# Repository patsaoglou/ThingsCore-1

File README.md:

#   ThingsCore 1

Linux capable mPCIe SOM based on the STM32MP1 MPU with 512MB DDR3+WIFI+ETHERNET capabilities

## Figures - Coming Soon

- Realistic View

- Stack-up (6-layer PCB)

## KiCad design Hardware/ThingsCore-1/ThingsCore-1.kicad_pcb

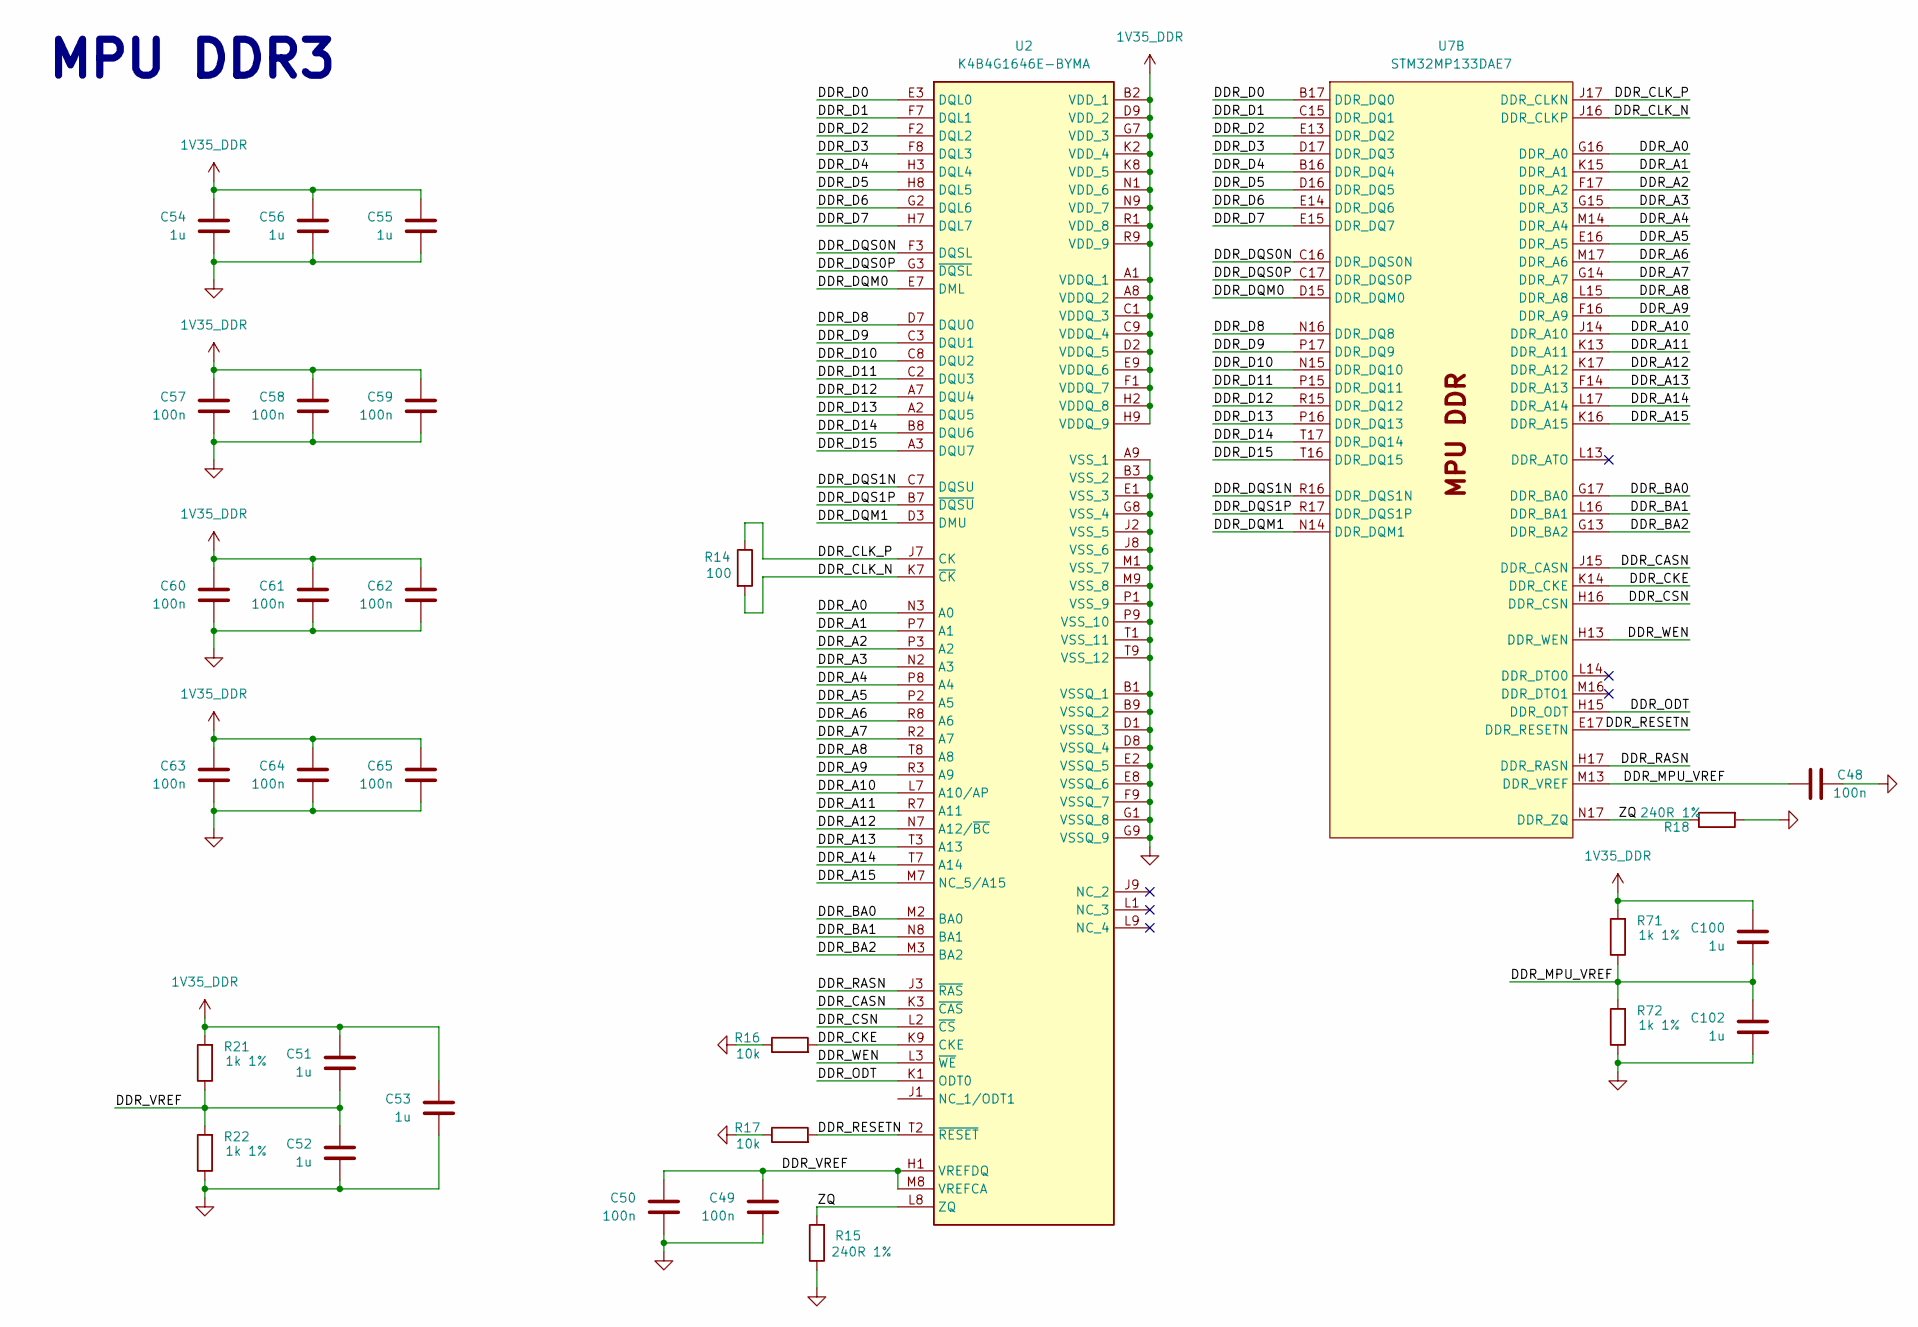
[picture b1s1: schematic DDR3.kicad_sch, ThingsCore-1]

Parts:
C48, C49, C50, C57, C58, C59, C60, C61, C62, C63, C64, C65: 100n; C_0402_1005Metric
C51, C52, C53, C54, C55, C56, C100, C102: 1u; C_0402_1005Metric
R14: 100; R_0402_1005Metric
R15, R18: 240R 1%; R_0402_1005Metric
R16, R17: 10k; R_0402_1005Metric
R21, R22, R71, R72: 1k 1%; R_0402_1005Metric
U2: K4B4G1646E-BYMA; BGA96C80P9X16_750X1330X120; Manufacturer_Part_Number K4B4G1646E-BYMA
U7: STM32MP133DAE7; LFBGA-289_14x14mm_Layout17x17_P0.8mm

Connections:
1V35_DDR: C51.2, C53.2, C54.2, C55.2, C56.2, C57.2, C58.2, C59.2, C60.2, C61.2, C62.2, C63.2, C64.2, C65.2, C100.2, R21.2, R71.2, U2.A1 (VDDQ_1), U2.A8 (VDDQ_2), U2.B2 (VDD_1), U2.C1 (VDDQ_3), U2.C9 (VDDQ_4), U2.D2 (VDDQ_5), U2.D9 (VDD_2), U2.E9 (VDDQ_6), U2.F1 (VDDQ_7), U2.G7 (VDD_3), U2.H2 (VDDQ_8), U2.H9 (VDDQ_9), U2.K2 (VDD_4), U2.K8 (VDD_5), U2.N1 (VDD_6), U2.N9 (VDD_7), U2.R1 (VDD_8), U2.R9 (VDD_9); also elsewhere on the board
/DDR3/DDR_A0: U2.N3 (A0), U7.G16 (DDR_A0)
/DDR3/DDR_A1: U2.P7 (A1), U7.K15 (DDR_A1)
/DDR3/DDR_A2: U2.P3 (A2), U7.F17 (DDR_A2)
/DDR3/DDR_A3: U2.N2 (A3), U7.G15 (DDR_A3)
/DDR3/DDR_A4: U2.P8 (A4), U7.M14 (DDR_A4)
/DDR3/DDR_A5: U2.P2 (A5), U7.E16 (DDR_A5)
/DDR3/DDR_A6: U2.R8 (A6), U7.M17 (DDR_A6)
/DDR3/DDR_A7: U2.R2 (A7), U7.G14 (DDR_A7)
/DDR3/DDR_A8: U2.T8 (A8), U7.L15 (DDR_A8)
/DDR3/DDR_A9: U2.R3 (A9), U7.F16 (DDR_A9)
/DDR3/DDR_A10: U2.L7 (A10/AP), U7.J14 (DDR_A10)
/DDR3/DDR_A11: U2.R7 (A11), U7.K13 (DDR_A11)
/DDR3/DDR_A12: U2.N7 (A12/~BC), U7.K17 (DDR_A12)
/DDR3/DDR_A13: U2.T3 (A13), U7.F14 (DDR_A13)
/DDR3/DDR_A14: U2.T7 (A14), U7.L17 (DDR_A14)
/DDR3/DDR_A15: U2.M7 (NC_5/A15), U7.K16 (DDR_A15)
/DDR3/DDR_BA0: U2.M2 (BA0), U7.G17 (DDR_BA0)
/DDR3/DDR_BA1: U2.N8 (BA1), U7.L16 (DDR_BA1)
/DDR3/DDR_BA2: U2.M3 (BA2), U7.G13 (DDR_BA2)
/DDR3/DDR_CASN: U2.K3 (~CAS), U7.J15 (DDR_CASN)
/DDR3/DDR_CKE: R16.2, U2.K9 (CKE), U7.K14 (DDR_CKE)
/DDR3/DDR_CLK_N: R14.2, U2.K7 (~CK), U7.J16 (DDR_CLKP)
/DDR3/DDR_CLK_P: R14.1, U2.J7 (CK), U7.J17 (DDR_CLKN)
/DDR3/DDR_CSN: U2.L2 (~CS), U7.H16 (DDR_CSN)
/DDR3/DDR_D0: U2.E3 (DQL0), U7.B17 (DDR_DQ0)
/DDR3/DDR_D1: U2.F7 (DQL1), U7.C15 (DDR_DQ1)
/DDR3/DDR_D2: U2.F2 (DQL2), U7.E13 (DDR_DQ2)
/DDR3/DDR_D3: U2.F8 (DQL3), U7.D17 (DDR_DQ3)
/DDR3/DDR_D4: U2.H3 (DQL4), U7.B16 (DDR_DQ4)
/DDR3/DDR_D5: U2.H8 (DQL5), U7.D16 (DDR_DQ5)
/DDR3/DDR_D6: U2.G2 (DQL6), U7.E14 (DDR_DQ6)
/DDR3/DDR_D7: U2.H7 (DQL7), U7.E15 (DDR_DQ7)
/DDR3/DDR_D8: U2.D7 (DQU0), U7.N16 (DDR_DQ8)
/DDR3/DDR_D9: U2.C3 (DQU1), U7.P17 (DDR_DQ9)
/DDR3/DDR_D10: U2.C8 (DQU2), U7.N15 (DDR_DQ10)
/DDR3/DDR_D11: U2.C2 (DQU3), U7.P15 (DDR_DQ11)
/DDR3/DDR_D12: U2.A7 (DQU4), U7.R15 (DDR_DQ12)
/DDR3/DDR_D13: U2.A2 (DQU5), U7.P16 (DDR_DQ13)
/DDR3/DDR_D14: U2.B8 (DQU6), U7.T17 (DDR_DQ14)
/DDR3/DDR_D15: U2.A3 (DQU7), U7.T16 (DDR_DQ15)
/DDR3/DDR_DQM0: U2.E7 (DML), U7.D15 (DDR_DQM0)
/DDR3/DDR_DQM1: U2.D3 (DMU), U7.N14 (DDR_DQM1)
/DDR3/DDR_DQS0N: U2.F3 (DQSL), U7.C16 (DDR_DQS0N)
/DDR3/DDR_DQS0P: U2.G3 (~DQSL), U7.C17 (DDR_DQS0P)
/DDR3/DDR_DQS1N: U2.C7 (DQSU), U7.R16 (DDR_DQS1N)
/DDR3/DDR_DQS1P: U2.B7 (~DQSU), U7.R17 (DDR_DQS1P)
/DDR3/DDR_MPU_VREF: C48.2, C100.1, C102.2, R71.1, R72.2, U7.M13 (DDR_VREF)
/DDR3/DDR_ODT: U2.K1 (ODT0), U7.H15 (DDR_ODT)
/DDR3/DDR_RASN: U2.J3 (~RAS), U7.H17 (DDR_RASN)
/DDR3/DDR_RESETN: R17.2, U2.T2 (~RESET), U7.E17 (DDR_RESETN)
/DDR3/DDR_VREF: C49.2, C50.2, C51.1, C52.2, R21.1, R22.2, U2.H1 (VREFDQ), U2.M8 (VREFCA)
/DDR3/DDR_WEN: U2.L3 (~WE), U7.H13 (DDR_WEN)
/DDR3/ZQ: R15.2, R18.1, U2.L8 (ZQ), U7.N17 (DDR_ZQ)
GND: C48.1, C49.1, C50.1, C52.1, C53.1, C54.1, C55.1, C56.1, C57.1, C58.1, C59.1, C60.1, C61.1, C62.1, C63.1, C64.1, C65.1, C102.1, R15.1, R16.1, R17.1, R18.2, R22.1, R72.1, U2.A9 (VSS_1), U2.B1 (VSSQ_1), U2.B3 (VSS_2), U2.B9 (VSSQ_2), U2.D1 (VSSQ_3), U2.D8 (VSSQ_4), U2.E1 (VSS_3), U2.E2 (VSSQ_5), U2.E8 (VSSQ_6), U2.F9 (VSSQ_7), U2.G1 (VSSQ_8), U2.G8 (VSS_4), U2.G9 (VSSQ_9), U2.J2 (VSS_5), U2.J8 (VSS_6), U2.M1 (VSS_7), U2.M9 (VSS_8), U2.P1 (VSS_9), U2.P9 (VSS_10), U2.T1 (VSS_11), U2.T9 (VSS_12); also elsewhere on the board

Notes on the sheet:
MPU DDR3

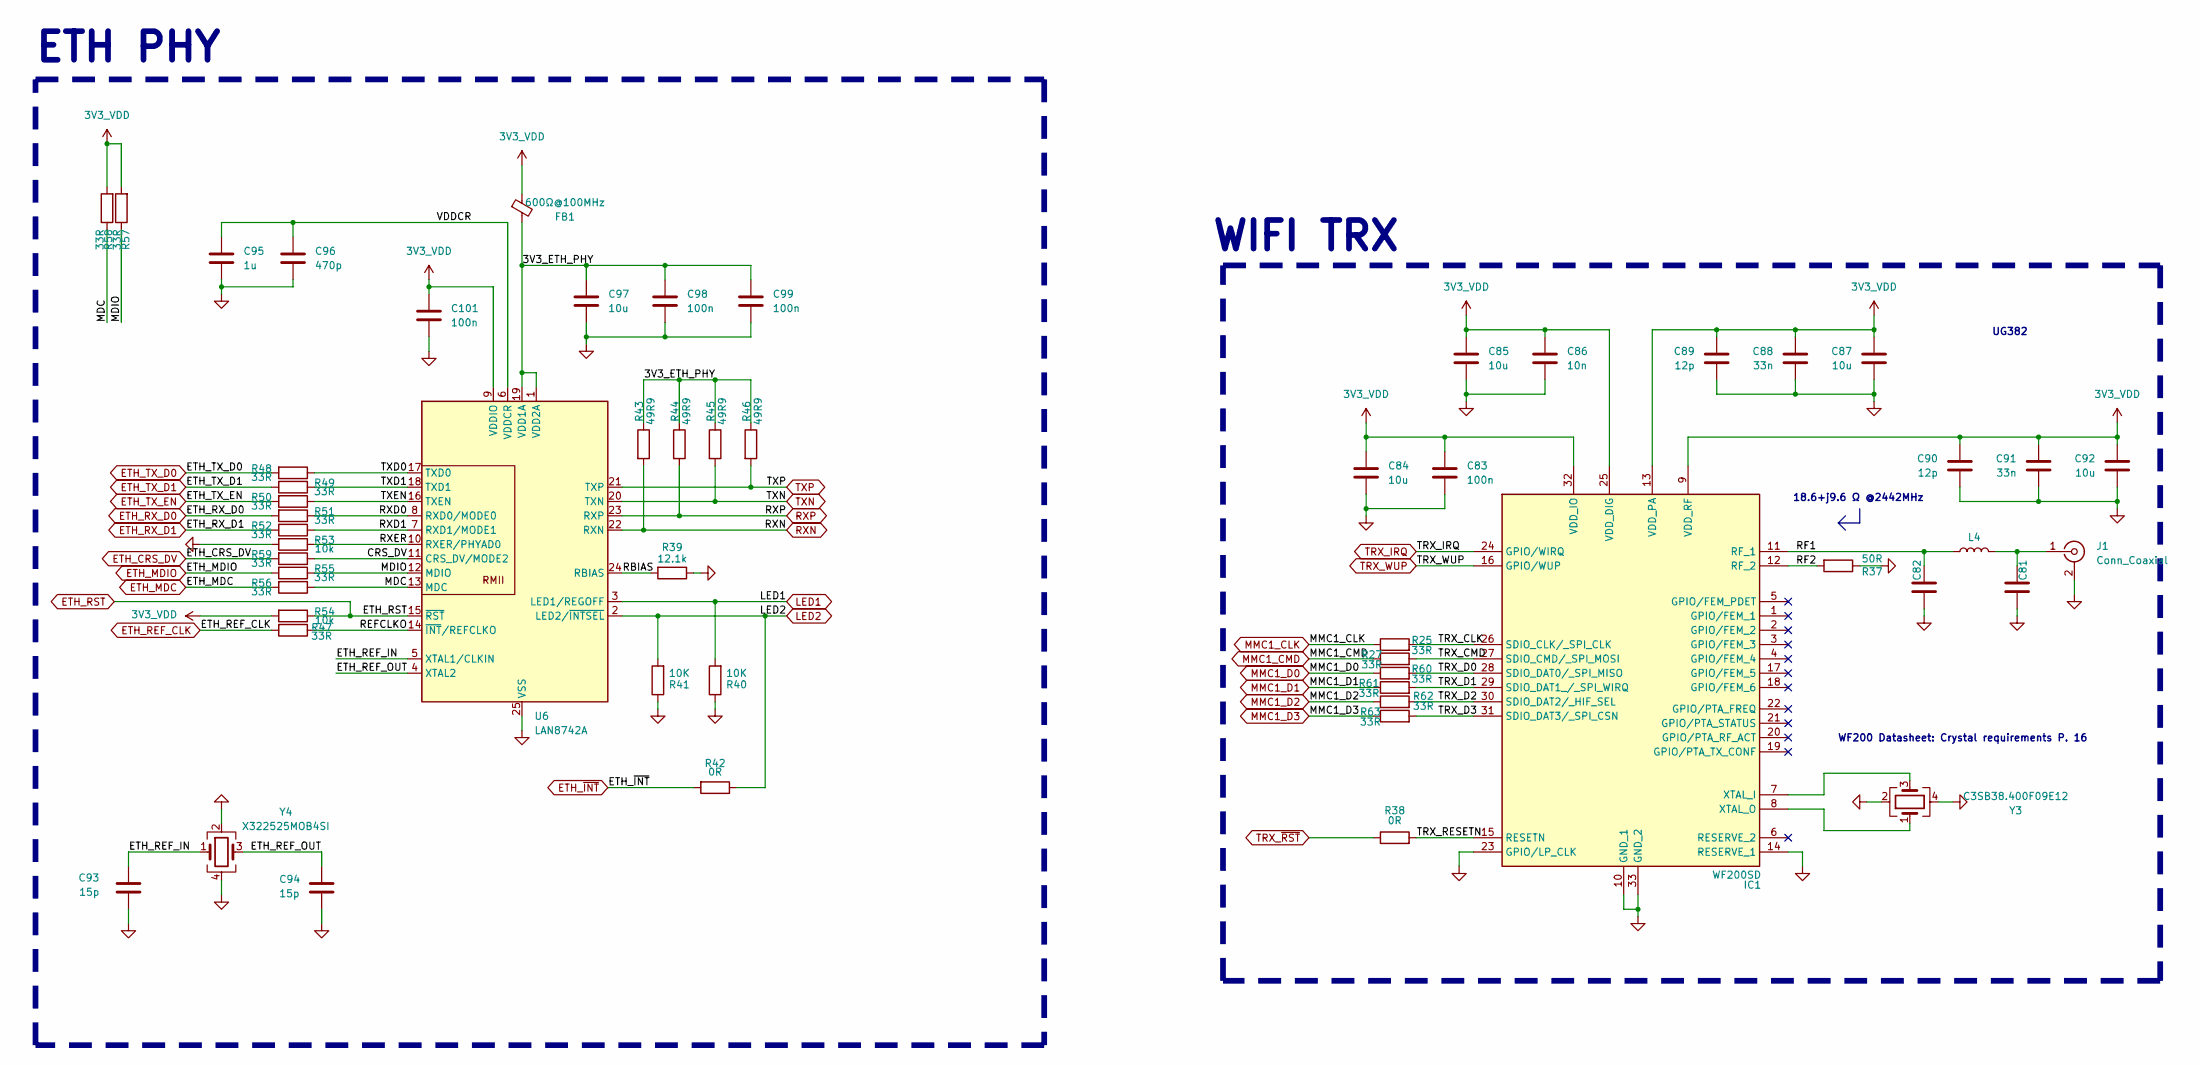
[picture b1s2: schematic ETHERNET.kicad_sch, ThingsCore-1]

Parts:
C81: C_0402_1005Metric
C82: 2.2u; C_0402_1005Metric
C83, C98, C99, C101: 100n; C_0402_1005Metric
C84, C85, C87, C92, C97: 10u; C_0402_1005Metric
C86: 10n; C_0402_1005Metric
C88, C91: 33n; C_0402_1005Metric
C89, C90: 12p; C_0402_1005Metric
C93, C94: 15p; C_0402_1005Metric
C95: 1u; C_0402_1005Metric
C96: 470p; C_0402_1005Metric
FB1: 600Ω@100MHz; L_0805_2012Metric
IC1: WF200SD; QFN40P400X400X90-33N-D; Mouser Part Number 634-WF200SD
J1: Conn_Coaxial; U.FL_Molex_MCRF_73412-0110_Vertical
L4: L_0402_1005Metric
R25, R27, R47, R48, R49, R50, R51, R52, R55, R56, R57, R58, R59, R60, R61, R62, R63: 33R; R_0402_1005Metric
R37: 50R; R_0402_1005Metric
R38, R42: 0R; R_0402_1005Metric
R39: 12.1k; R_0402_1005Metric
R40, R41: 10K; R_0402_1005Metric
R43, R44, R45, R46: 49R9; R_0402_1005Metric
R53, R54: 10k; R_0402_1005Metric
U6: LAN8742A; VQFN-24-1EP_4x4mm_P0.5mm_EP2.45x2.45mm
Y3: C3SB38.400F09E12; Crystal_SMD_3225-4Pin_3.2x2.5mm
Y4: X322525MOB4SI; Crystal_SMD_3225-4Pin_3.2x2.5mm

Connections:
3V3_VDD: C83.2, C84.2, C85.2, C86.2, C87.2, C88.2, C89.2, C90.2, C91.2, C92.2, C101.2, FB1.1, IC1.9 (VDD_RF), IC1.13 (VDD_PA), IC1.25 (VDD_DIG), IC1.32 (VDD_IO), R54.2, R57.2, R58.2, U6.9 (VDDIO); also elsewhere on the board
/NETWORKING/3V3_ETH_PHY: C97.2, C98.2, C99.2, FB1.2, R43.1, R44.1, R45.1, R46.1, U6.1 (VDD2A), U6.19 (VDD1A)
/NETWORKING/CRS_DV: R59.1, U6.11 (CRS_DV/MODE2)
/NETWORKING/ETH_REF_IN: C93.2, U6.5 (XTAL1/CLKIN), Y4.1
/NETWORKING/ETH_REF_OUT: C94.2, U6.4 (XTAL2), Y4.3
/NETWORKING/MDC: R56.1, R58.1, U6.13 (MDC)
/NETWORKING/MDIO: R55.1, R57.1, U6.12 (MDIO)
/NETWORKING/RBIAS: R39.2, U6.24 (RBIAS)
/NETWORKING/REFCLKO: R47.1, U6.14 (~INT/REFCLKO)
/NETWORKING/RF1: C82.1, IC1.11 (RF_1), L4.1
/NETWORKING/RF2: IC1.12 (RF_2), R37.2
/NETWORKING/RXD0: R51.1, U6.8 (RXD0/MODE0)
/NETWORKING/RXD1: R52.1, U6.7 (RXD1/MODE1)
/NETWORKING/RXER: R53.1, U6.10 (RXER/PHYAD0)
/NETWORKING/TRX_CLK: IC1.26 (SDIO_CLK/_SPI_CLK), R25.2
/NETWORKING/TRX_CMD: IC1.27 (SDIO_CMD/_SPI_MOSI), R27.2
/NETWORKING/TRX_D0: IC1.28 (SDIO_DAT0/_SPI_MISO), R60.2
/NETWORKING/TRX_D1: IC1.29 (SDIO_DAT1_/_SPI_WIRQ), R61.2
/NETWORKING/TRX_D2: IC1.30 (SDIO_DAT2/_HIF_SEL), R62.2
/NETWORKING/TRX_D3: IC1.31 (SDIO_DAT3/_SPI_CSN), R63.2
/NETWORKING/TRX_RESETN: IC1.15 (RESETN), R38.2
/NETWORKING/TXD0: R48.1, U6.17 (TXD0)
/NETWORKING/TXD1: R49.1, U6.18 (TXD1)
/NETWORKING/TXEN: R50.1, U6.16 (TXEN)
/NETWORKING/VDDCR: C95.2, C96.2, U6.6 (VDDCR)
ETH_CRS_DV: R59.2; also elsewhere on the board
ETH_MDC: R56.2; also elsewhere on the board
ETH_MDIO: R55.2; also elsewhere on the board
ETH_REF_CLK: R47.2; also elsewhere on the board
ETH_RST: R54.1, U6.15 (~RST); also elsewhere on the board
ETH_RX_D0: R51.2; also elsewhere on the board
ETH_RX_D1: R52.2; also elsewhere on the board
ETH_TX_D0: R48.2; also elsewhere on the board
ETH_TX_D1: R49.2; also elsewhere on the board
ETH_TX_EN: R50.2; also elsewhere on the board
ETH_~INT: R42.2; also elsewhere on the board
GND: C81.2, C82.2, C83.1, C84.1, C85.1, C86.1, C87.1, C88.1, C89.1, C90.1, C91.1, C92.1, C93.1, C94.1, C95.1, C96.1, C97.1, C98.1, C99.1, C101.1, IC1.10 (GND_1), IC1.14 (RESERVE_1), IC1.23 (GPIO/LP_CLK), IC1.33 (GND_2), J1.2 (Ext), R37.1, R39.1, R40.1, R41.1, R53.2, U6.25 (VSS), Y3.2, Y3.4, Y4.2, Y4.4; also elsewhere on the board
LED1: R40.2, U6.3 (LED1/REGOFF); also elsewhere on the board
LED2: R41.2, R42.1, U6.2 (LED2/~INTSEL); also elsewhere on the board
MMC1_CLK: R25.1; also elsewhere on the board
MMC1_CMD: R27.1; also elsewhere on the board
MMC1_D0: R60.1; also elsewhere on the board
MMC1_D1: R61.1; also elsewhere on the board
MMC1_D2: R62.1; also elsewhere on the board
MMC1_D3: R63.1; also elsewhere on the board
unnamed: IC1.7 (XTAL_I), Y3.3
unnamed: IC1.8 (XTAL_O), Y3.1
unnamed: C81.1, J1.1 (In), L4.2
RXN: R43.2, U6.22 (RXN); also elsewhere on the board
RXP: R44.2, U6.23 (RXP); also elsewhere on the board
TRX_IRQ: IC1.24 (GPIO/WIRQ); also elsewhere on the board
TRX_WUP: IC1.16 (GPIO/WUP); also elsewhere on the board
TRX_~RST: R38.1
TXN: R45.2, U6.20 (TXN); also elsewhere on the board
TXP: R46.2, U6.21 (TXP); also elsewhere on the board

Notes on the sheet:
UG382
18.6+j9.6 Ω @2442MHz
WF200 Datasheet: Crystal requirements P. 16
ETH PHY
WIFI TRX

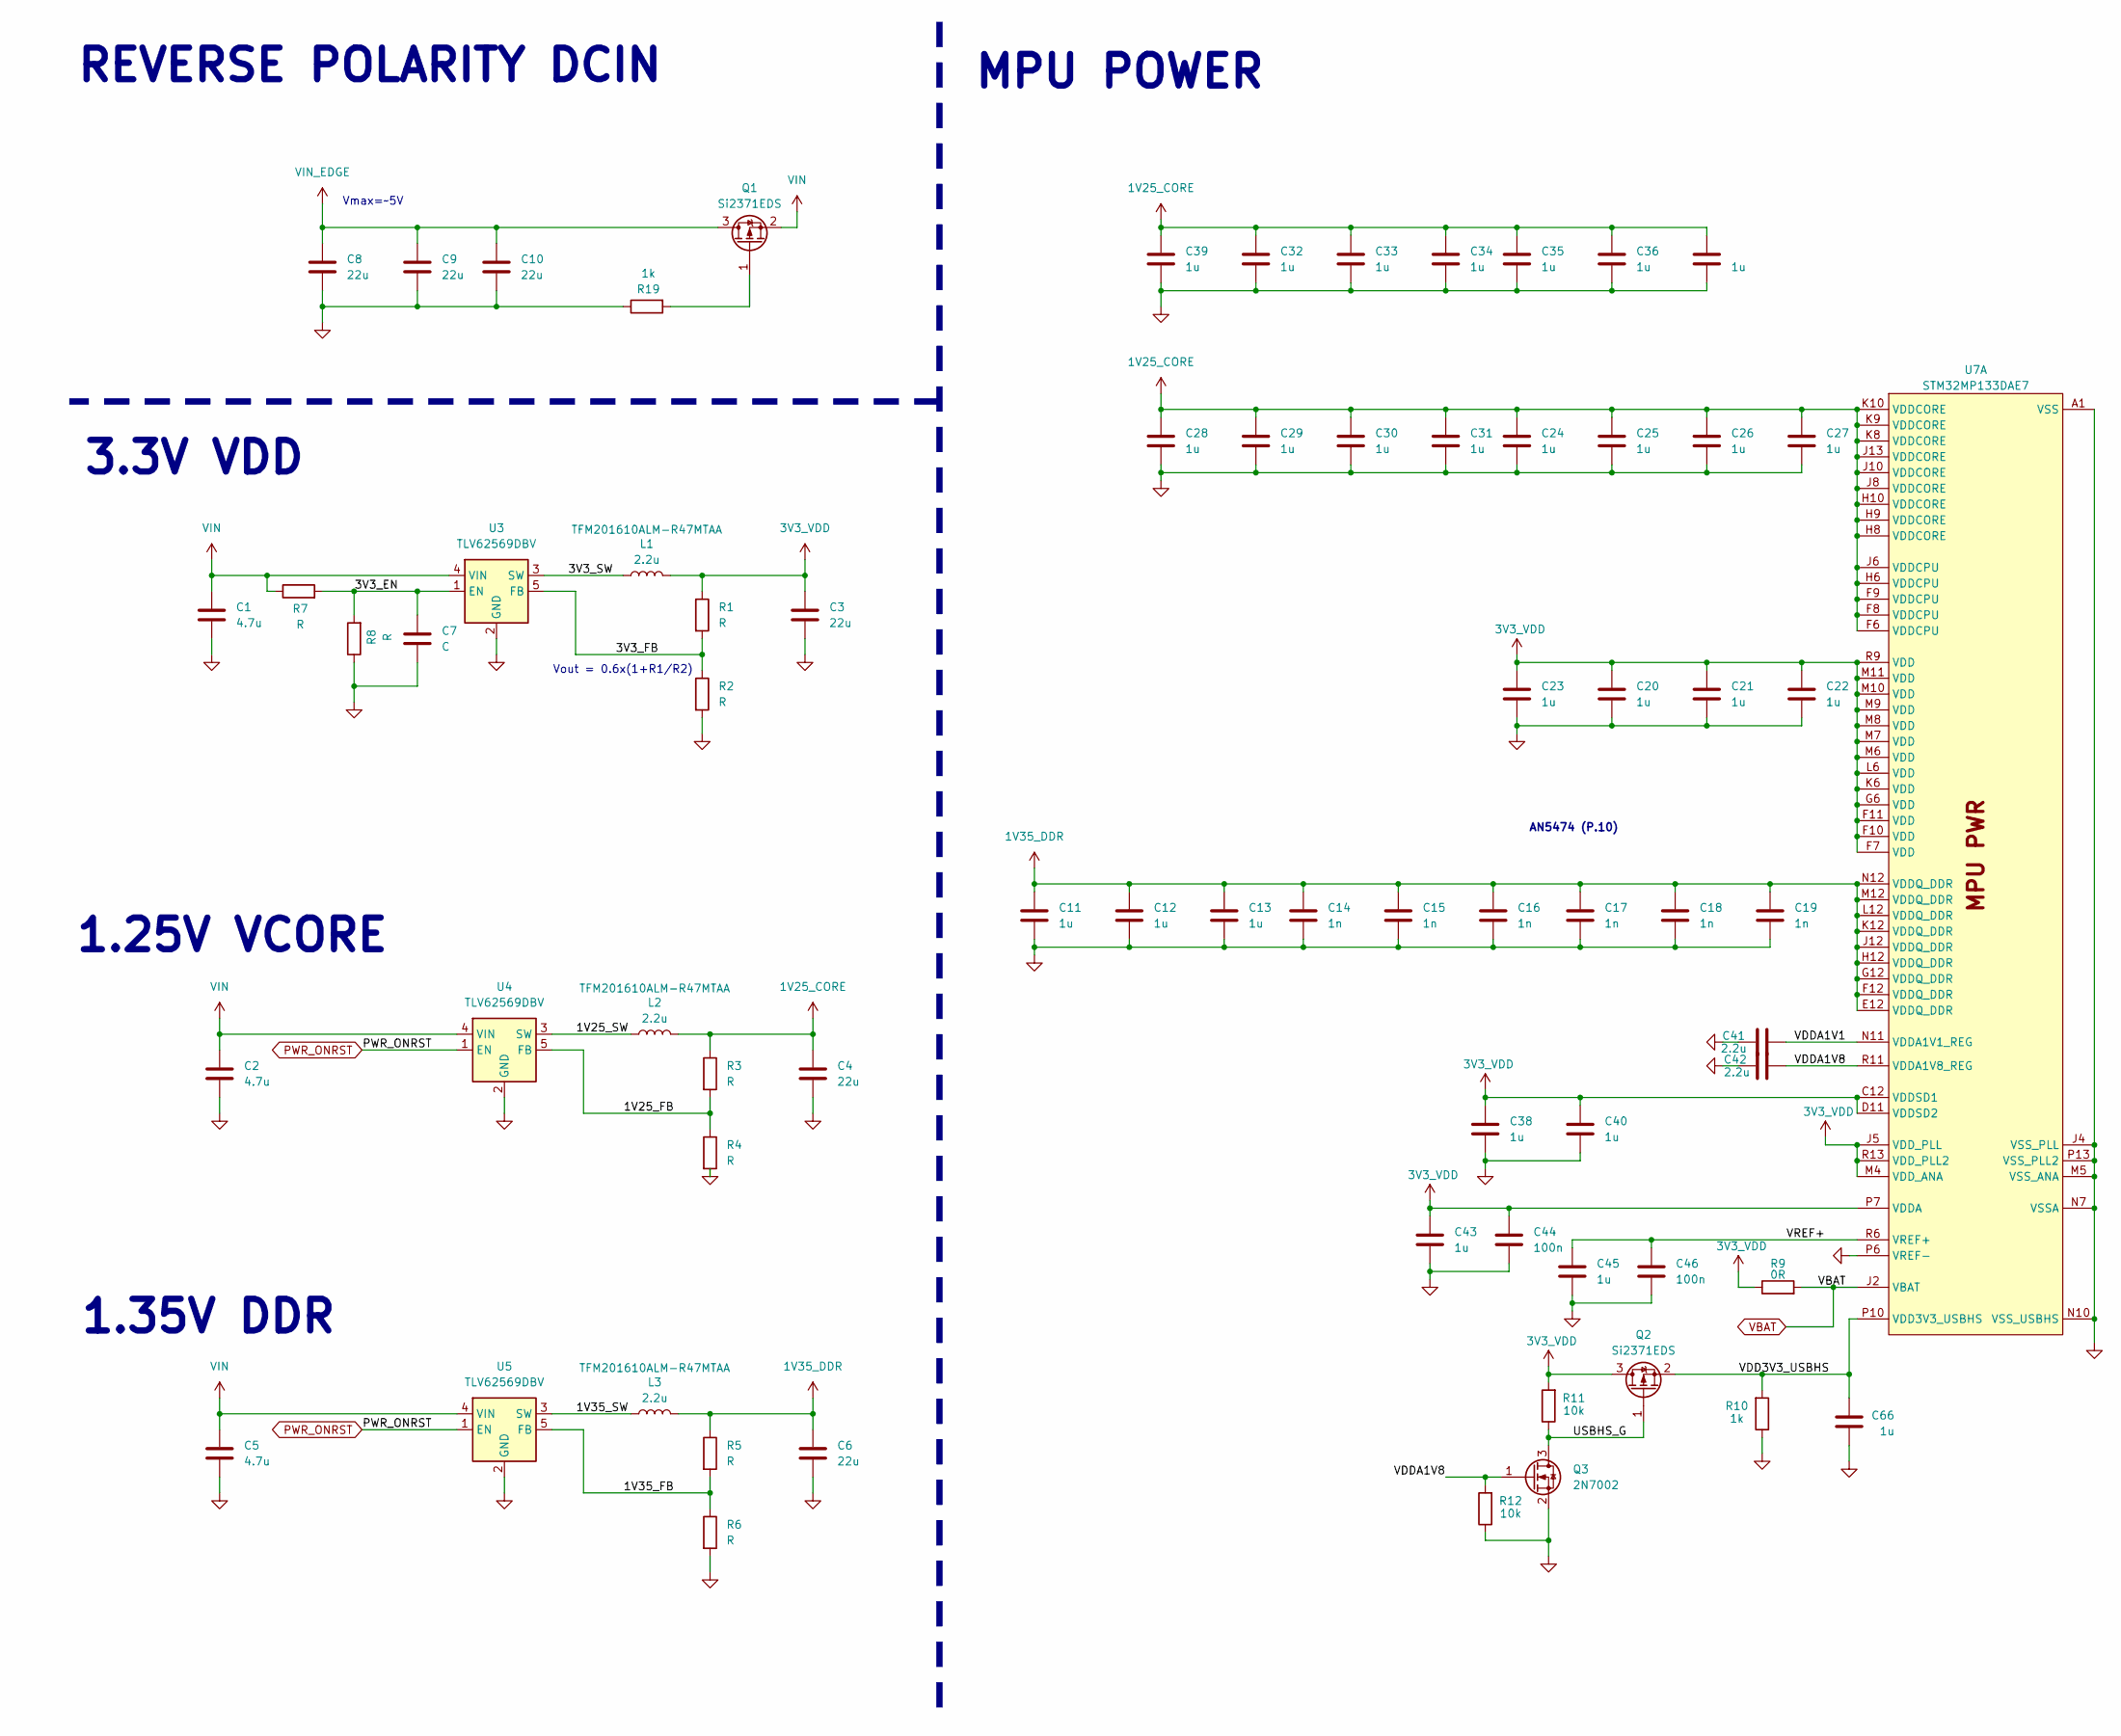
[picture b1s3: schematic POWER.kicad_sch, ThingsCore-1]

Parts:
C1, C2, C5: 4.7u; C_0603_1608Metric
C3, C4, C6, C8, C9, C10: 22u; C_0805_2012Metric
C7: C; C_0402_1005Metric
C11, C12, C13, C20, C21, C22, C23, C24, C25, C26, C27, C28, C29, C30, C31, C32, C33, C34, C35, C36, C37, C38, C39, C40, C43, C45, C66: 1u; C_0402_1005Metric
C14, C15, C16, C17, C18, C19: 1n; C_0402_1005Metric
C41, C42: 2.2u; C_0402_1005Metric
C44, C46: 100n; C_0402_1005Metric
L1, L2, L3: 2.2u; L_0805_2016
Q1, Q2: Si2371EDS; SOT-23
Q3: 2N7002; SOT-23
R1, R2, R3, R4, R5, R6, R7, R8: R; R_0402_1005Metric
R9: 0R; R_0402_1005Metric
R10, R19: 1k; R_0402_1005Metric
R11, R12: 10k; R_0402_1005Metric
U3, U4, U5: TLV62569DBV; SOT-23-5_HandSoldering
U7: STM32MP133DAE7; LFBGA-289_14x14mm_Layout17x17_P0.8mm

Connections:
1V25_CORE: C4.2, C24.2, C25.2, C26.2, C27.2, C28.2, C29.2, C30.2, C31.2, C32.2, C33.2, C34.2, C35.2, C36.2, C37.2, C39.2, L2.2, R3.1, U7.F6 (VDDCPU), U7.F8 (VDDCPU), U7.F9 (VDDCPU), U7.H6 (VDDCPU), U7.H8 (VDDCORE), U7.H9 (VDDCORE), U7.H10 (VDDCORE), U7.J6 (VDDCPU), U7.J8 (VDDCORE), U7.J10 (VDDCORE), U7.J13 (VDDCORE), U7.K8 (VDDCORE), U7.K9 (VDDCORE), U7.K10 (VDDCORE)
1V35_DDR: C6.2, C11.2, C12.2, C13.2, C14.2, C15.2, C16.2, C17.2, C18.2, C19.2, L3.2, R5.1, U7.E12 (VDDQ_DDR), U7.F12 (VDDQ_DDR), U7.G12 (VDDQ_DDR), U7.H12 (VDDQ_DDR), U7.J12 (VDDQ_DDR), U7.K12 (VDDQ_DDR), U7.L12 (VDDQ_DDR), U7.M12 (VDDQ_DDR), U7.N12 (VDDQ_DDR); also elsewhere on the board
3V3_VDD: C3.2, C20.2, C21.2, C22.2, C23.2, C38.2, C40.2, C43.2, C44.2, L1.2, Q2.3 (D), R1.1, R9.1, R11.2, U7.C12 (VDDSD1), U7.D11 (VDDSD2), U7.F7 (VDD), U7.F10 (VDD), U7.F11 (VDD), U7.G6 (VDD), U7.J5 (VDD_PLL), U7.K6 (VDD), U7.L6 (VDD), U7.M4 (VDD_ANA), U7.M6 (VDD), U7.M7 (VDD), U7.M8 (VDD), U7.M9 (VDD), U7.M10 (VDD), U7.M11 (VDD), U7.P7 (VDDA), U7.R9 (VDD), U7.R13 (VDD_PLL2); also elsewhere on the board
/POWER/1V25_FB: R3.2, R4.1, U4.5 (FB)
/POWER/1V25_SW: L2.1, U4.3 (SW)
/POWER/1V35_FB: R5.2, R6.1, U5.5 (FB)
/POWER/1V35_SW: L3.1, U5.3 (SW)
/POWER/3V3_EN: C7.2, R7.2, R8.2, U3.1 (EN)
/POWER/3V3_FB: R1.2, R2.1, U3.5 (FB)
/POWER/3V3_SW: L1.1, U3.3 (SW)
/POWER/USBHS_G: Q2.1 (G), Q3.3 (D), R11.1
/POWER/VDD3V3_USBHS: C66.2, Q2.2 (S), R10.2, U7.P10 (VDD3V3_USBHS)
/POWER/VDDA1V1: C41.1, U7.N11 (VDDA1V1_REG)
/POWER/VDDA1V8: C42.1, Q3.1 (G), R12.2, U7.R11 (VDDA1V8_REG)
/POWER/VREF+: C45.2, C46.2, U7.R6 (VREF+)
GND: C1.1, C2.1, C3.1, C4.1, C5.1, C6.1, C7.1, C8.1, C9.1, C10.1, C11.1, C12.1, C13.1, C14.1, C15.1, C16.1, C17.1, C18.1, C19.1, C20.1, C21.1, C22.1, C23.1, C24.1, C25.1, C26.1, C27.1, C28.1, C29.1, C30.1, C31.1, C32.1, C33.1, C34.1, C35.1, C36.1, C37.1, C38.1, C39.1, C40.1, C41.2, C42.2, C43.1, C44.1, C45.1, C46.1, C66.1, Q3.2 (S), R2.2, R4.2, R6.2, R8.1, R10.1, R12.1, R19.1, U3.2 (GND), U4.2 (GND), U5.2 (GND), U7.A1 (VSS), U7.A17 (VSS), U7.C8 (VSS), U7.D3 (VSS), U7.D12 (VSS), U7.E5 (VSS), U7.F13 (VSS), U7.F15 (VSS), U7.G7 (VSS), U7.G8 (VSS), U7.G9 (VSS), U7.G10 (VSS), U7.G11 (VSS), U7.H7 (VSS), U7.H11 (VSS), U7.H14 (VSS), U7.J4 (VSS_PLL), U7.J7 (VSS), U7.J9 (VSS), U7.J11 (VSS), U7.K3 (VSS), U7.K7 (VSS), U7.K11 (VSS), U7.L7 (VSS), U7.L8 (VSS), U7.L9 (VSS), U7.L10 (VSS), U7.L11 (VSS), U7.M5 (VSS_ANA), U7.M15 (VSS), U7.N4 (VSS), U7.N7 (VSSA), U7.N10 (VSS_USBHS), U7.P6 (VREF-), U7.P11 (VSS), U7.P13 (VSS_PLL2), U7.R5 (VSS), U7.R8 (VSS), U7.U1 (VSS), U7.U17 (VSS); also elsewhere on the board
unnamed: Q1.1 (G), R19.2
PWR_ONRST: U4.1 (EN), U5.1 (EN); also elsewhere on the board
VBAT: R9.2, U7.J2 (VBAT); also elsewhere on the board
VIN: C1.2, C2.2, C5.2, Q1.2 (S), R7.1, U3.4 (VIN), U4.4 (VIN), U5.4 (VIN)
VIN_EDGE: C8.2, C9.2, C10.2, Q1.3 (D); also elsewhere on the board

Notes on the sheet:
AN5474 (P.10)
1.25V VCORE
Vmax=~5V
1.35V DDR
REVERSE POLARITY DCIN
MPU POWER
3.3V VDD
Vout = 0.6x(1+R1/R2)

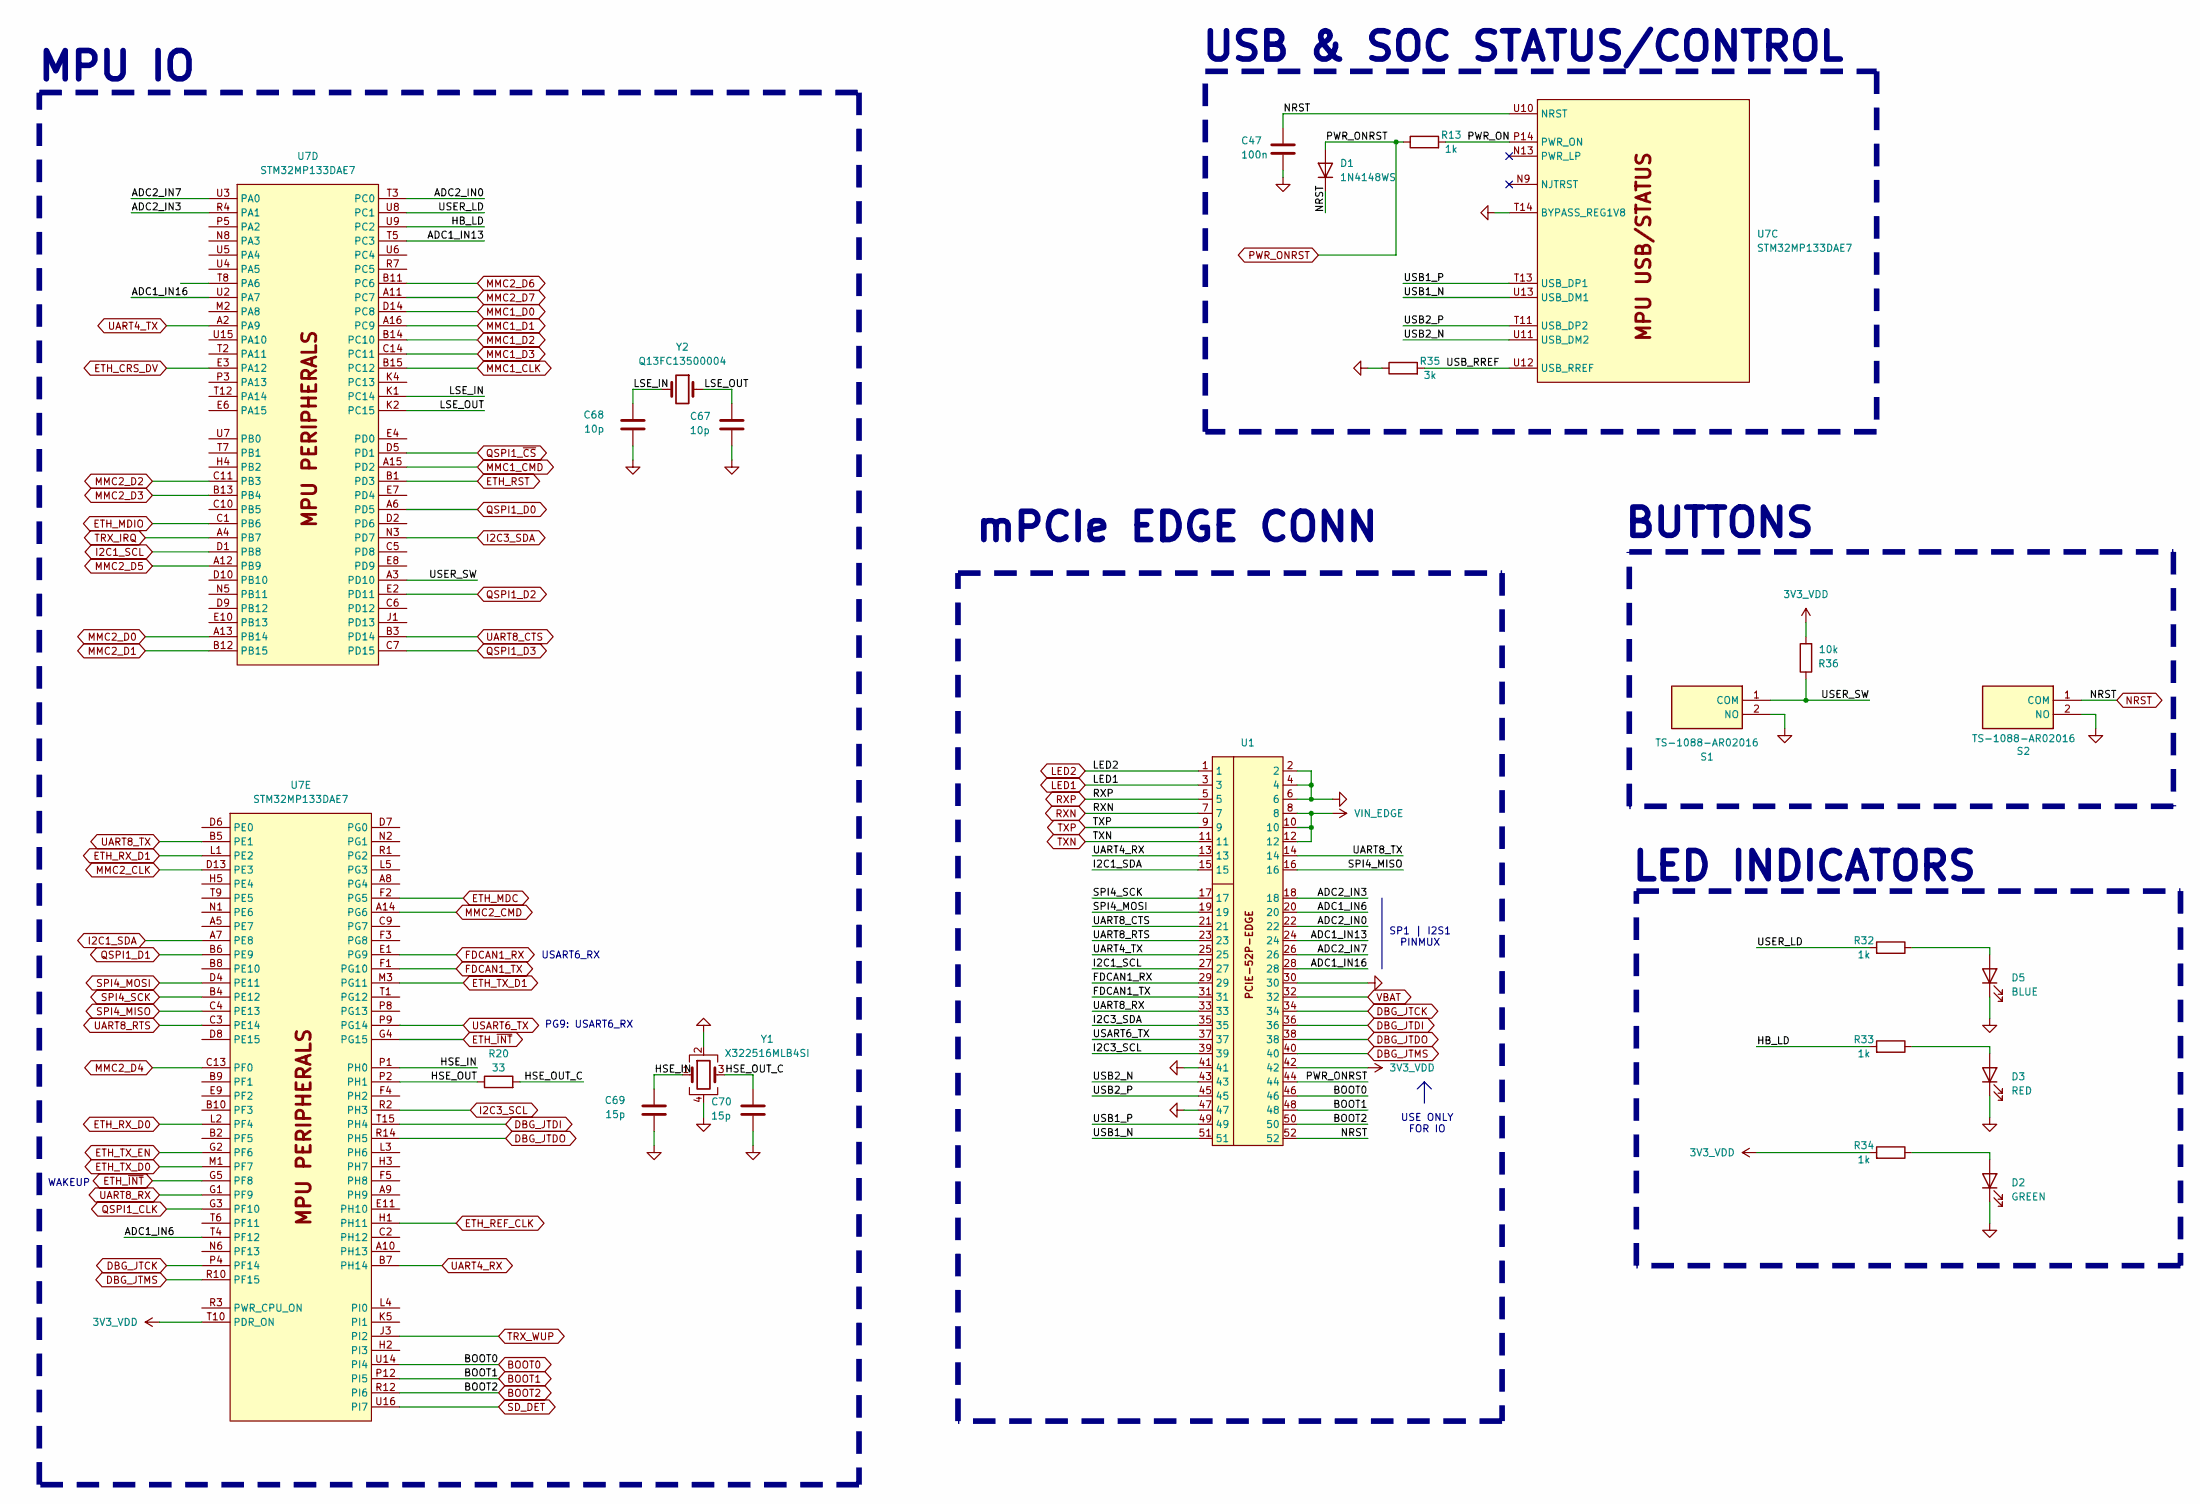
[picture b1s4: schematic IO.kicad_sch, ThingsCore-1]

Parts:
C47: 100n; C_0402_1005Metric
C67, C68: 10p; C_0402_1005Metric
C69, C70: 15p; C_0402_1005Metric
D1: 1N4148WS; D_SOD-323
D2: GREEN; LED_0603_1608Metric
D3: RED; LED_0603_1608Metric
D5: BLUE; LED_0603_1608Metric
R13, R32, R33, R34: 1k; R_0402_1005Metric
R20: 33; R_0402_1005Metric
R35: 3k; R_0402_1005Metric
R36: 10k; R_0402_1005Metric
S1, S2: TS-1088-AR02016; TS1088AR02016; Manufacturer_Part_Number TS-1088-AR02016
U1: PCIE-52P-EDGEFULL
U7: STM32MP133DAE7; LFBGA-289_14x14mm_Layout17x17_P0.8mm
Y1: X322516MLB4SI; Crystal_SMD_3225-4Pin_3.2x2.5mm
Y2: Q13FC13500004; Crystal_SMD_3215-2Pin_3.2x1.5mm

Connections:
3V3_VDD: R34.2, R36.2, U1.42, U7.T10 (PDR_ON); also elsewhere on the board
/MPU-IO/ADC1_IN6: U1.20, U7.T4 (PF12)
/MPU-IO/ADC1_IN13: U1.24, U7.T5 (PC3)
/MPU-IO/ADC1_IN16: U1.28, U7.U2 (PA7)
/MPU-IO/ADC2_IN0: U1.22, U7.T3 (PC0)
/MPU-IO/ADC2_IN3: U1.18, U7.R4 (PA1)
/MPU-IO/ADC2_IN7: U1.26, U7.U3 (PA0)
/MPU-IO/HB_LD: R33.2, U7.U9 (PC2)
/MPU-IO/HSE_IN: C69.2, U7.P1 (PH0), Y1.1
/MPU-IO/HSE_OUT: R20.1, U7.P2 (PH1)
/MPU-IO/HSE_OUT_C: C70.2, R20.2, Y1.3
/MPU-IO/LSE_IN: C68.2, U7.K1 (PC14), Y2.2
/MPU-IO/LSE_OUT: C67.2, U7.K2 (PC15), Y2.1
/MPU-IO/PWR_ON: R13.2, U7.P14 (PWR_ON)
/MPU-IO/USB1_N: U1.51, U7.U13 (USB_DM1)
/MPU-IO/USB1_P: U1.49, U7.T13 (USB_DP1)
/MPU-IO/USB2_N: U1.43, U7.U11 (USB_DM2)
/MPU-IO/USB2_P: U1.45, U7.T11 (USB_DP2)
/MPU-IO/USB_RREF: R35.2, U7.U12 (USB_RREF)
/MPU-IO/USER_LD: R32.2, U7.U8 (PC1)
/MPU-IO/USER_SW: R36.1, S1.1 (COM), U7.A3 (PD10)
BOOT0: U1.46, U7.U14 (PI4)
BOOT1: U1.48, U7.P12 (PI5)
BOOT2: U1.50, U7.R12 (PI6)
DBG_JTCK: U1.34, U7.P4 (PF14)
DBG_JTDI: U1.36, U7.T15 (PH4)
DBG_JTDO: U1.38, U7.R14 (PH5)
DBG_JTMS: U1.40, U7.R10 (PF15)
ETH_CRS_DV: U7.E3 (PA12); also elsewhere on the board
ETH_MDC: U7.F2 (PG5); also elsewhere on the board
ETH_MDIO: U7.C1 (PB6); also elsewhere on the board
ETH_REF_CLK: U7.H1 (PH11); also elsewhere on the board
ETH_RST: U7.B1 (PD3); also elsewhere on the board
ETH_RX_D0: U7.L2 (PF4); also elsewhere on the board
ETH_RX_D1: U7.L1 (PE2); also elsewhere on the board
ETH_TX_D0: U7.M1 (PF7); also elsewhere on the board
ETH_TX_D1: U7.M3 (PG11); also elsewhere on the board
ETH_TX_EN: U7.G2 (PF6); also elsewhere on the board
ETH_~INT: U7.G4 (PG15), U7.G5 (PF8); also elsewhere on the board
FDCAN1_RX: U1.29, U7.E1 (PG9)
FDCAN1_TX: U1.31, U7.F1 (PG10)
GND: C47.1, C67.1, C68.1, C69.1, C70.1, D2.1 (K), D3.1 (K), D5.1 (K), R35.1, S1.2 (NO), S2.2 (NO), U1.2, U1.4, U1.6, U1.30, U1.41, U1.47, U7.T14 (BYPASS_REG1V8), Y1.2, Y1.4; also elsewhere on the board
I2C1_SCL: U1.27, U7.D1 (PB8)
I2C1_SDA: U1.15, U7.A7 (PE8)
I2C3_SCL: U1.39, U7.R2 (PH3)
I2C3_SDA: U1.35, U7.N3 (PD7)
LED1: U1.3; also elsewhere on the board
LED2: U1.1; also elsewhere on the board
MMC1_CLK: U7.B15 (PC12); also elsewhere on the board
MMC1_CMD: U7.A15 (PD2); also elsewhere on the board
MMC1_D0: U7.D14 (PC8); also elsewhere on the board
MMC1_D1: U7.A16 (PC9); also elsewhere on the board
MMC1_D2: U7.B14 (PC10); also elsewhere on the board
MMC1_D3: U7.C14 (PC11); also elsewhere on the board
MMC2_CLK: U7.D13 (PE3); also elsewhere on the board
MMC2_CMD: U7.A14 (PG6); also elsewhere on the board
MMC2_D0: U7.A13 (PB14); also elsewhere on the board
MMC2_D1: U7.B12 (PB15); also elsewhere on the board
MMC2_D2: U7.C11 (PB3); also elsewhere on the board
MMC2_D3: U7.B13 (PB4); also elsewhere on the board
MMC2_D4: U7.C13 (PF0); also elsewhere on the board
MMC2_D5: U7.A12 (PB9); also elsewhere on the board
MMC2_D6: U7.B11 (PC6); also elsewhere on the board
MMC2_D7: U7.A11 (PC7); also elsewhere on the board
NRST: C47.2, D1.1 (K), S2.1 (COM), U1.52, U7.U10 (NRST)
unnamed: D2.2 (A), R34.1
unnamed: D3.2 (A), R33.1
unnamed: D5.2 (A), R32.1
PWR_ONRST: D1.2 (A), R13.1, U1.44; also elsewhere on the board
QSPI1_CLK: U7.G3 (PF10); also elsewhere on the board
QSPI1_D0: U7.A6 (PD5); also elsewhere on the board
QSPI1_D1: U7.B6 (PE9); also elsewhere on the board
QSPI1_D2: U7.E2 (PD11); also elsewhere on the board
QSPI1_D3: U7.C7 (PD15); also elsewhere on the board
QSPI1_~CS: U7.D5 (PD1); also elsewhere on the board
RXN: U1.7; also elsewhere on the board
RXP: U1.5; also elsewhere on the board
SD_DET: U7.U16 (PI7); also elsewhere on the board
SPI4_MISO: U1.16, U7.C4 (PE13)
SPI4_MOSI: U1.19, U7.D4 (PE11)
SPI4_SCK: U1.17, U7.B4 (PE12)
TRX_IRQ: U7.A4 (PB7); also elsewhere on the board
TRX_WUP: U7.J3 (PI2); also elsewhere on the board
TXN: U1.11; also elsewhere on the board
TXP: U1.9; also elsewhere on the board
UART4_RX: U1.13, U7.B7 (PH14)
UART4_TX: U1.25, U7.A2 (PA9)
UART8_CTS: U1.21, U7.B3 (PD14)
UART8_RTS: U1.23, U7.C3 (PE14)
UART8_RX: U1.33, U7.G1 (PF9)
UART8_TX: U1.14, U7.B5 (PE1)
USART6_TX: U1.37, U7.P9 (PG14)
VBAT: U1.32; also elsewhere on the board
VIN_EDGE: U1.8, U1.10, U1.12; also elsewhere on the board

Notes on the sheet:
USB & SOC STATUS/CONTROL
USE ONLY FOR IO
BUTTONS
PG9: USART6_RX
USART6_RX
SP1 | I2S1 PINMUX
MPU IO
WAKEUP
LED INDICATORS
mPCIe EDGE CONN
